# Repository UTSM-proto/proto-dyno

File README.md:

# proto-dyno

Simple Python dyno load controller for ATORCH DL24/DL24P-style USB serial electronic loads.

The app treats the load bank as a variable road load / hill resistance for a motor-generator dyno. It presents a watts slider, reads live telemetry, and uses conservative software safety clamps.

## Safety Defaults

This software intentionally defaults far below advertised DL24 ratings:

- max power: 50 W
- max current: 3 A
- max voltage: 36 V
- minimum voltage: 2.5 V
- max temperature: 70 C
- update rate: 2 Hz
- telemetry timeout: 2 seconds

Cheap DL24-style loads are often advertised around 150 W / 180 W, but those ratings are not safe continuous dyno limits. Start low, keep airflow on the load, and validate with external meters.

The app immediately attempts to stop the load if:

- voltage rises above the configured maximum
- voltage falls below the configured minimum while load is enabled
- temperature exceeds the configured maximum
- serial telemetry is lost for more than 2 seconds

## Protocol Status

The known public DL24/PX100-style serial protocol supports:

- output on/off
- current setpoint
- voltage cutoff setpoint
- voltage telemetry
- current telemetry
- temperature telemetry

Native constant-power mode control is not exposed by the simple working Python examples inspected for this repo. `proto-dyno` therefore defaults to constant-power emulation:

```text
I_target = P_target / V_measured
```

The computed current is clamped to the configured current and power limits before being sent to the load.

## Install

Python 3.10+ is recommended.

```powershell
python -m venv .venv
.\.venv\Scripts\Activate.ps1
python -m pip install -r requirements.txt
```

Tkinter ships with normal python.org Windows installers. If your Python build lacks Tkinter, install a standard CPython build.

## Run

```powershell
python -m proto_dyno.app
```

For a specific port:

```powershell
python -m proto_dyno.app --port COM7
```

To list likely devices:

```powershell
python -m proto_dyno.cli list
```

## Notes

- Plug in the DL24 before launching the app.
- The app looks for likely USB serial adapters such as CH340, USB-SERIAL, CP210x, and FTDI devices.
- The load starts disabled. Move the slider, then press `Enable Load`.
- Press `Stop Load` before changing wiring.
- Keep hardware current limits, fuses, and external meters in the setup. Software clamps are a backup, not the primary protection.

## Dyno Joulemeter Firmware

This repo also includes Arduino firmware for the prototype dyno joulemeter:

```text
dyno_joulemeter_firmware/dyno_joulemeter.ino
```

That sketch reads voltage and ACS712 current through an ADS1115, displays live V/I/P/J on an SSD1306 OLED, and logs CSV-style serial rows for dyno runs. See `dyno_joulemeter_firmware/README.md` for wiring, calibration constants, and library requirements.

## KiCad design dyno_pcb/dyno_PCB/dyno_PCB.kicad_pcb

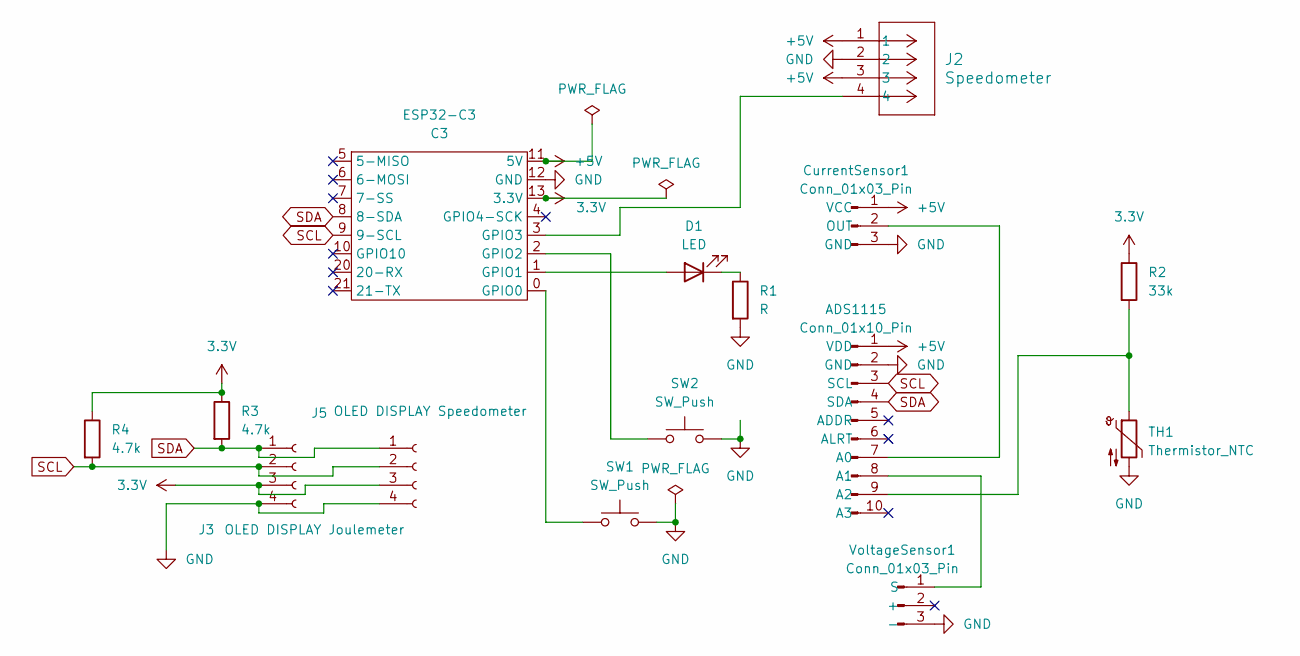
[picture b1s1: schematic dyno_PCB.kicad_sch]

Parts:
ADS1115: Conn_01x10_Pin; PinSocket_1x10_P2.54mm_Vertical
CurrentSensor1: Conn_01x03_Pin; PinSocket_1x03_P2.54mm_Vertical
D1: LED; LED_D5.0mm
ESP32-C3: C3; ESP32C3
J2: Speedometer; Molex_Mini-Fit_Jr_5566-04A_2x02_P4.20mm_Vertical
J3: OLED DISPLAY Joulemeter; footprintOLEDKicad
J5: OLED DISPLAY Speedometer; footprintOLEDKicad
R1: R; R_Axial_DIN0204_L3.6mm_D1.6mm_P5.08mm_Horizontal
R2: 33k; R_Axial_DIN0204_L3.6mm_D1.6mm_P5.08mm_Horizontal
R3, R4: 4.7k; R_Axial_DIN0204_L3.6mm_D1.6mm_P5.08mm_Horizontal
SW1, SW2: SW_Push; SW_PUSH_6mm_H5mm
TH1: Thermistor_NTC; PinSocket_1x02_P2.54mm_Vertical
VoltageSensor1: Conn_01x03_Pin; PinSocket_1x03_P2.54mm_Vertical

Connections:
3.3V: ESP32-C3.13 (3.3V), J3.3, J5.3, R2.1, R3.1, R4.1
+5V: ADS1115.1 (VDD), CurrentSensor1.1 (VCC), ESP32-C3.11 (5V), J2.1, J2.3
GND: ADS1115.2 (GND), CurrentSensor1.3 (GND), ESP32-C3.12 (GND), J2.2, J3.4, J5.4, R1.2, SW1.2, SW2.2, TH1.2, VoltageSensor1.3 (-)
unnamed: ADS1115.7 (A0), CurrentSensor1.2 (OUT)
unnamed: ADS1115.8 (A1), VoltageSensor1.1 (S)
unnamed: ADS1115.9 (A2), R2.2, TH1.1
unnamed: D1.2 (A), ESP32-C3.1 (GPIO1)
unnamed: D1.1 (K), R1.1
unnamed: ESP32-C3.0 (GPIO0), SW1.1
unnamed: ESP32-C3.2 (GPIO2), SW2.1
unnamed: ESP32-C3.3 (GPIO3), J2.4
SCL: ADS1115.3 (SCL), ESP32-C3.9 (9-SCL), J3.2, J5.2, R4.2
SDA: ADS1115.4 (SDA), ESP32-C3.8 (8-SDA), J3.1, J5.1, R3.2

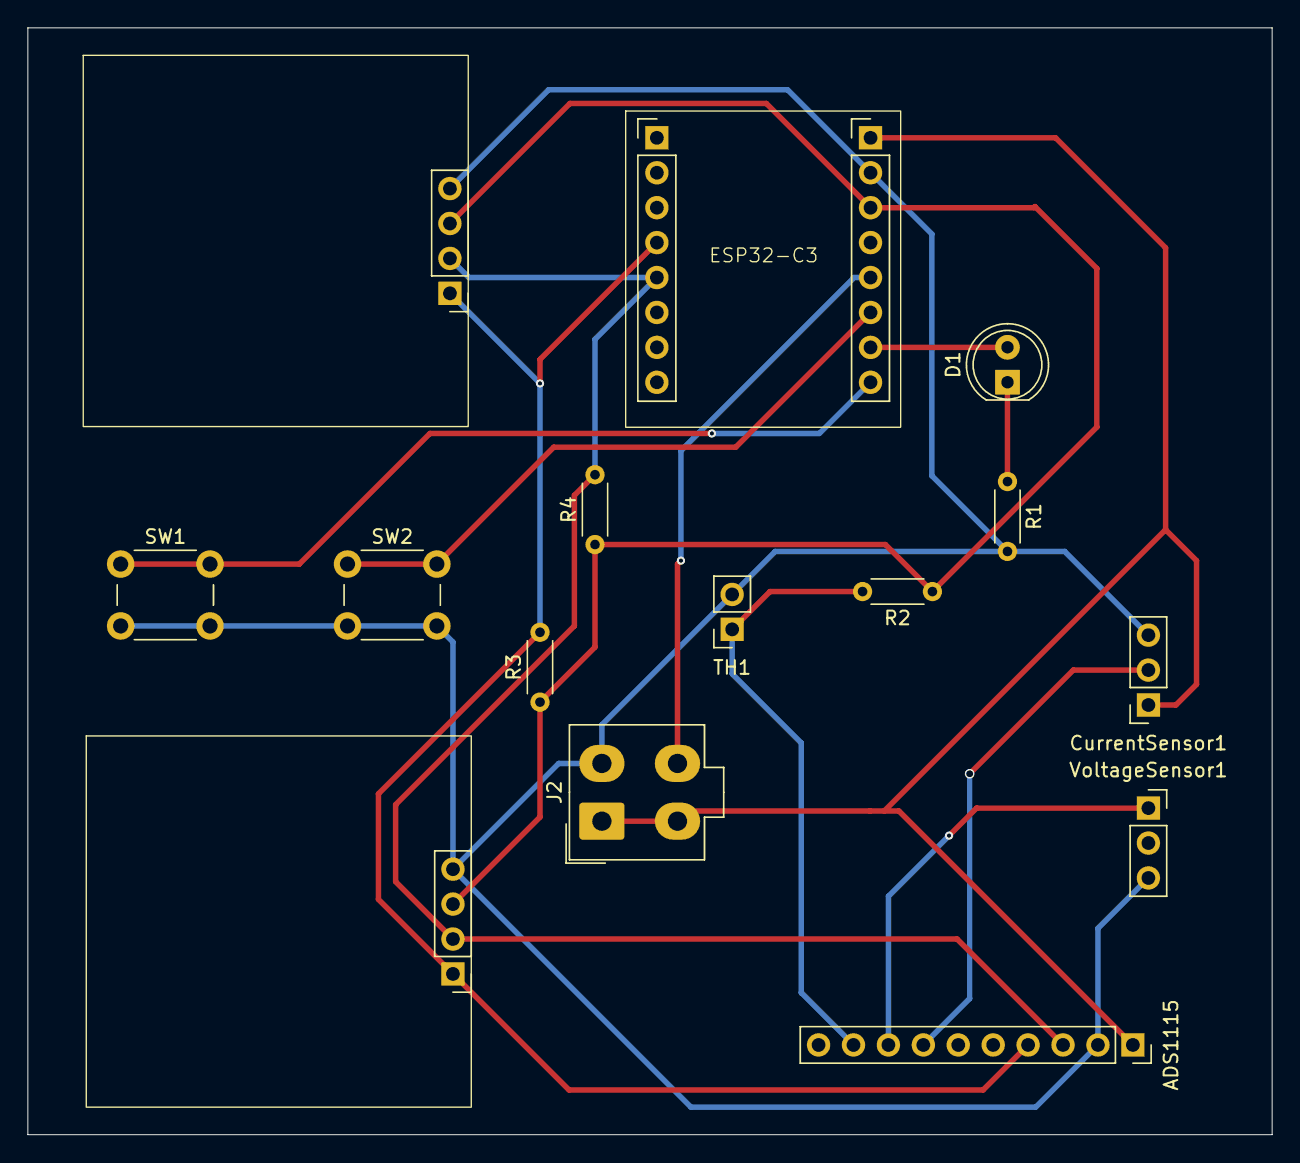
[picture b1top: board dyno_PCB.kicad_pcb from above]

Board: 2 copper layers, 90.5 x 80.5 mm, 15 parts (0 on the bottom side), 13 nets.

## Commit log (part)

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2026-06-25 Add DL24 dyno load slider app
